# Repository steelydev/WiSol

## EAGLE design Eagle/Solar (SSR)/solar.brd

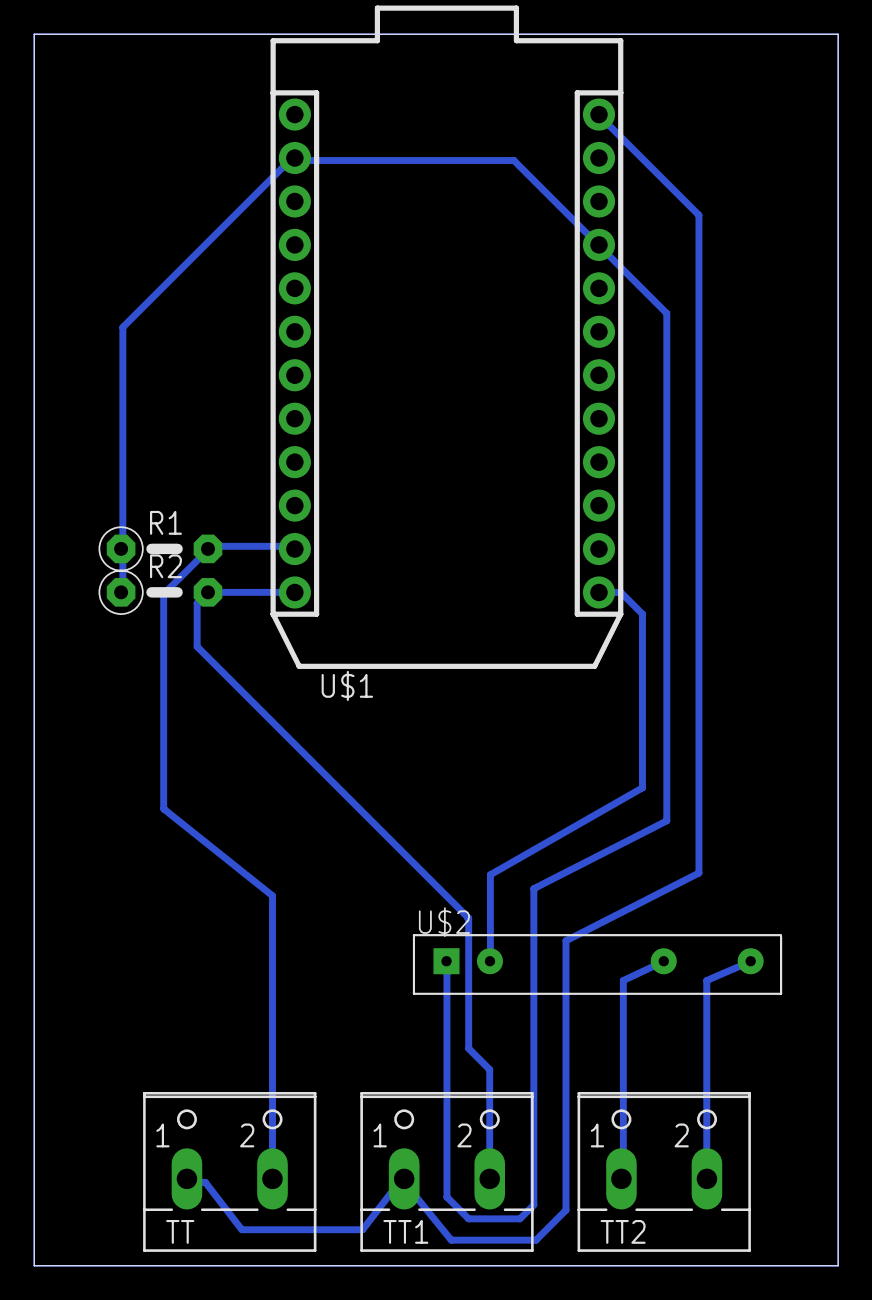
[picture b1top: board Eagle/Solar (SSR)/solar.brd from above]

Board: 1 copper layer, 47.0 x 72.0 mm, 7 parts (0 on the bottom side), 4 nets.

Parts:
R1, R2: 0207/5V
TT, TT1, TT2: W237-102
U$1: PHOTON_WITH_HEADERS; PHOTON
U$2: SIP-POWER

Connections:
3V3: TT.1, TT1.1, U$1.24
GND: R1.1, R2.1, U$1.2, U$1.21
unnamed: R1.2, TT.2, U$1.11
unnamed: R2.2, TT1.2, U$1.12

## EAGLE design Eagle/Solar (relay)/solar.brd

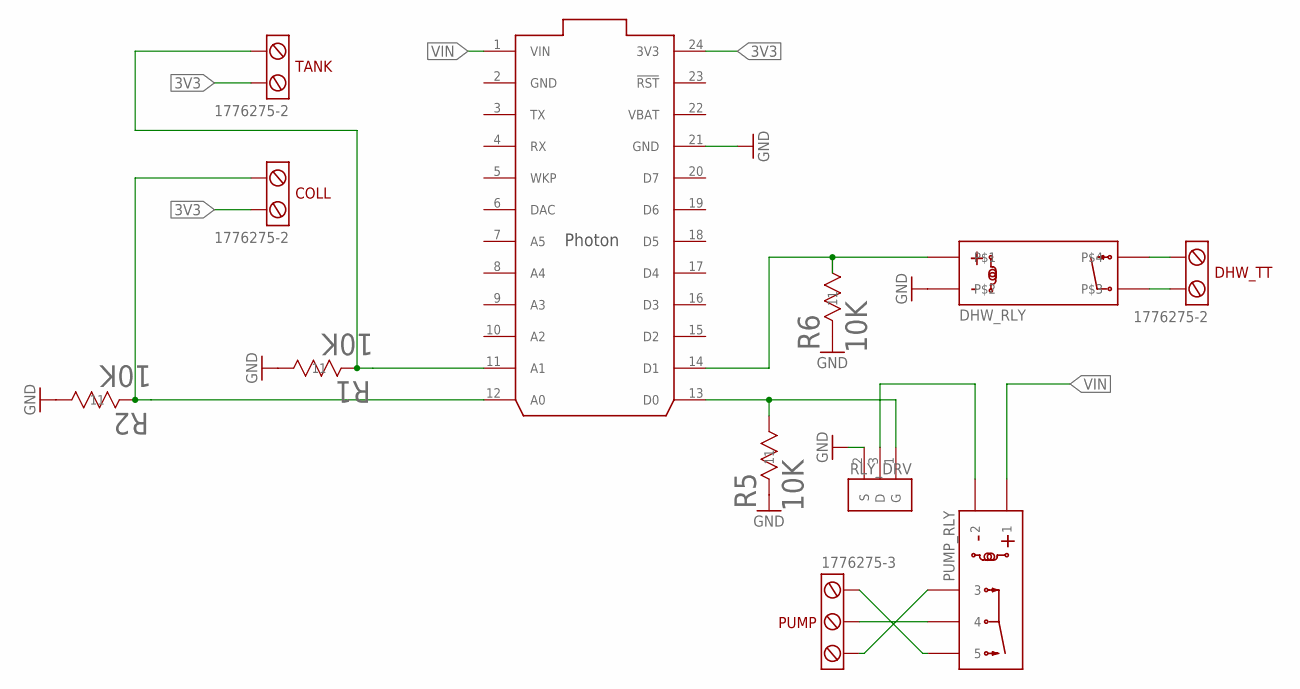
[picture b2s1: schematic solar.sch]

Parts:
COLL: 1776275-2; TERM-BLOCK-3.5MM-2
DHW_RLY: CPC1017N; SOP04
DHW_TT: 1776275-2; TERM-BLOCK-3.5MM-2
PARTICLE: PHOTON_WITH_HEADERS; PHOTON
PUMP: 1776275-3; TERM-BLOCK-3.5MM-3
PUMP_RLY: PE014005; RELAY5-PE_CO
R1, R2, R5, R6: 10K; 0805-M
RLY_DRV: NTR4003N; SOT23
TANK: 1776275-2; TERM-BLOCK-3.5MM-2

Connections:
3V3: COLL.P$1, PARTICLE.24 (3V3), TANK.P$1
A0: COLL.P$2, PARTICLE.12 (A0), R2.1 (11)
A1: PARTICLE.11 (A1), R1.1 (11), TANK.P$2
COM: PUMP.P$2, PUMP_RLY.11 (4)
D0: PARTICLE.13 (D0), R5.2 (22), RLY_DRV.1 (G)
D1: DHW_RLY.P$1, PARTICLE.14 (D1), R6.2 (22)
GND: DHW_RLY.P$2, PARTICLE.2 (GND), PARTICLE.21 (GND), R1.2 (22), R2.2 (22), R5.1 (11), R6.1 (11), RLY_DRV.2 (S)
unnamed: PUMP_RLY.A2 (2), RLY_DRV.3 (D)
unnamed: DHW_RLY.P$4, DHW_TT.P$2
unnamed: DHW_RLY.P$3, DHW_TT.P$1
NC: PUMP.P$3, PUMP_RLY.12 (3)
NO: PUMP.P$1, PUMP_RLY.14 (5)
VBAT: PARTICLE.22 (VBAT)
VIN: PARTICLE.1 (VIN), PUMP_RLY.A1 (1)

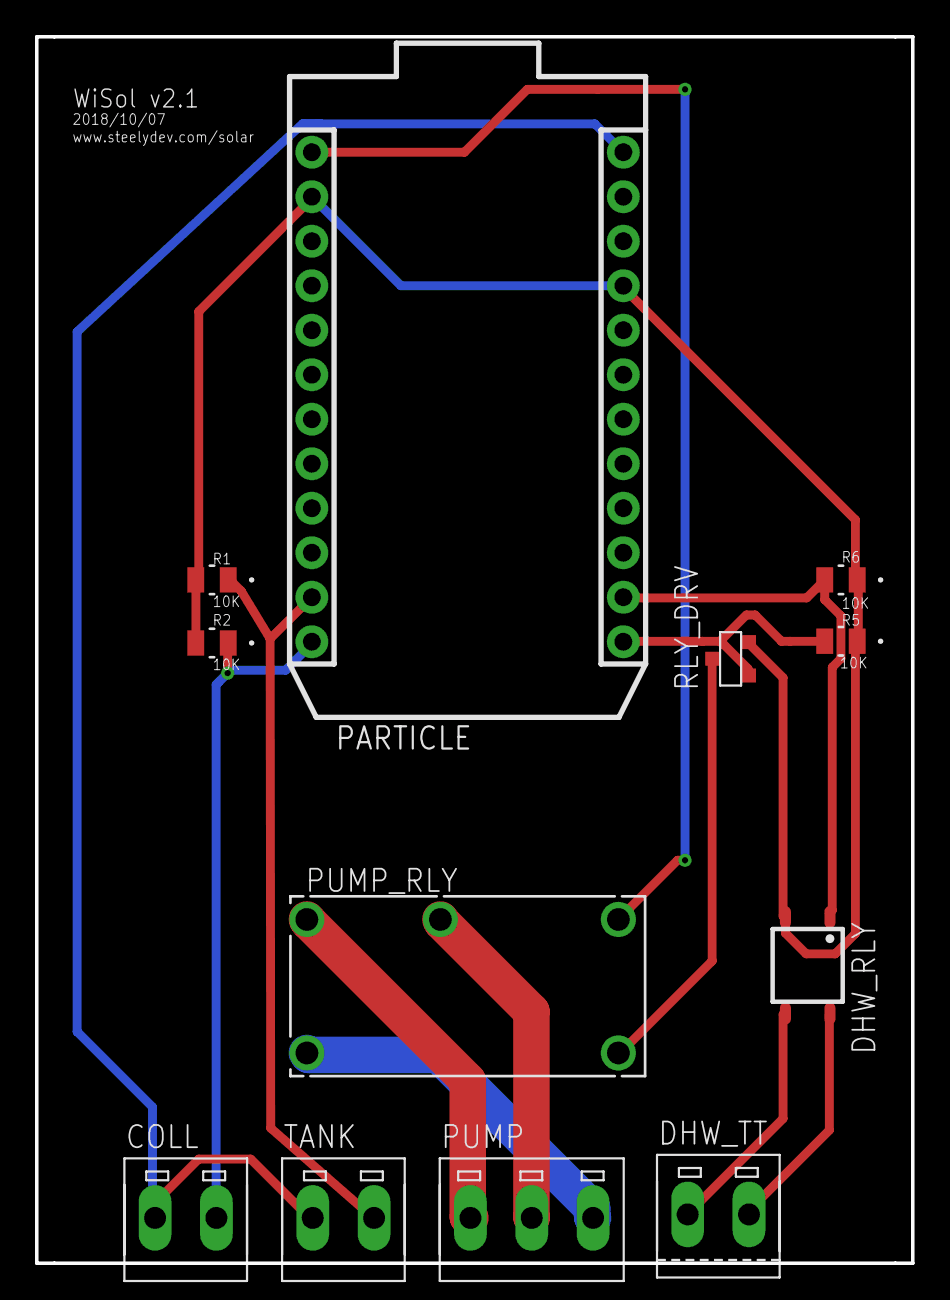
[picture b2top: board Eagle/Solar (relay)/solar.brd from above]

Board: 2 copper layers, 50.0 x 70.0 mm, 12 parts (0 on the bottom side), 13 nets.

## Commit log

2020-09-05 Pull Eagle files into repo
